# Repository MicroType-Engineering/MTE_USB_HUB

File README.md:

MTE_USB_HUB

As designed on the MicroType Engineering's YouTube series: https://youtu.be/uzqXgHHZUUs

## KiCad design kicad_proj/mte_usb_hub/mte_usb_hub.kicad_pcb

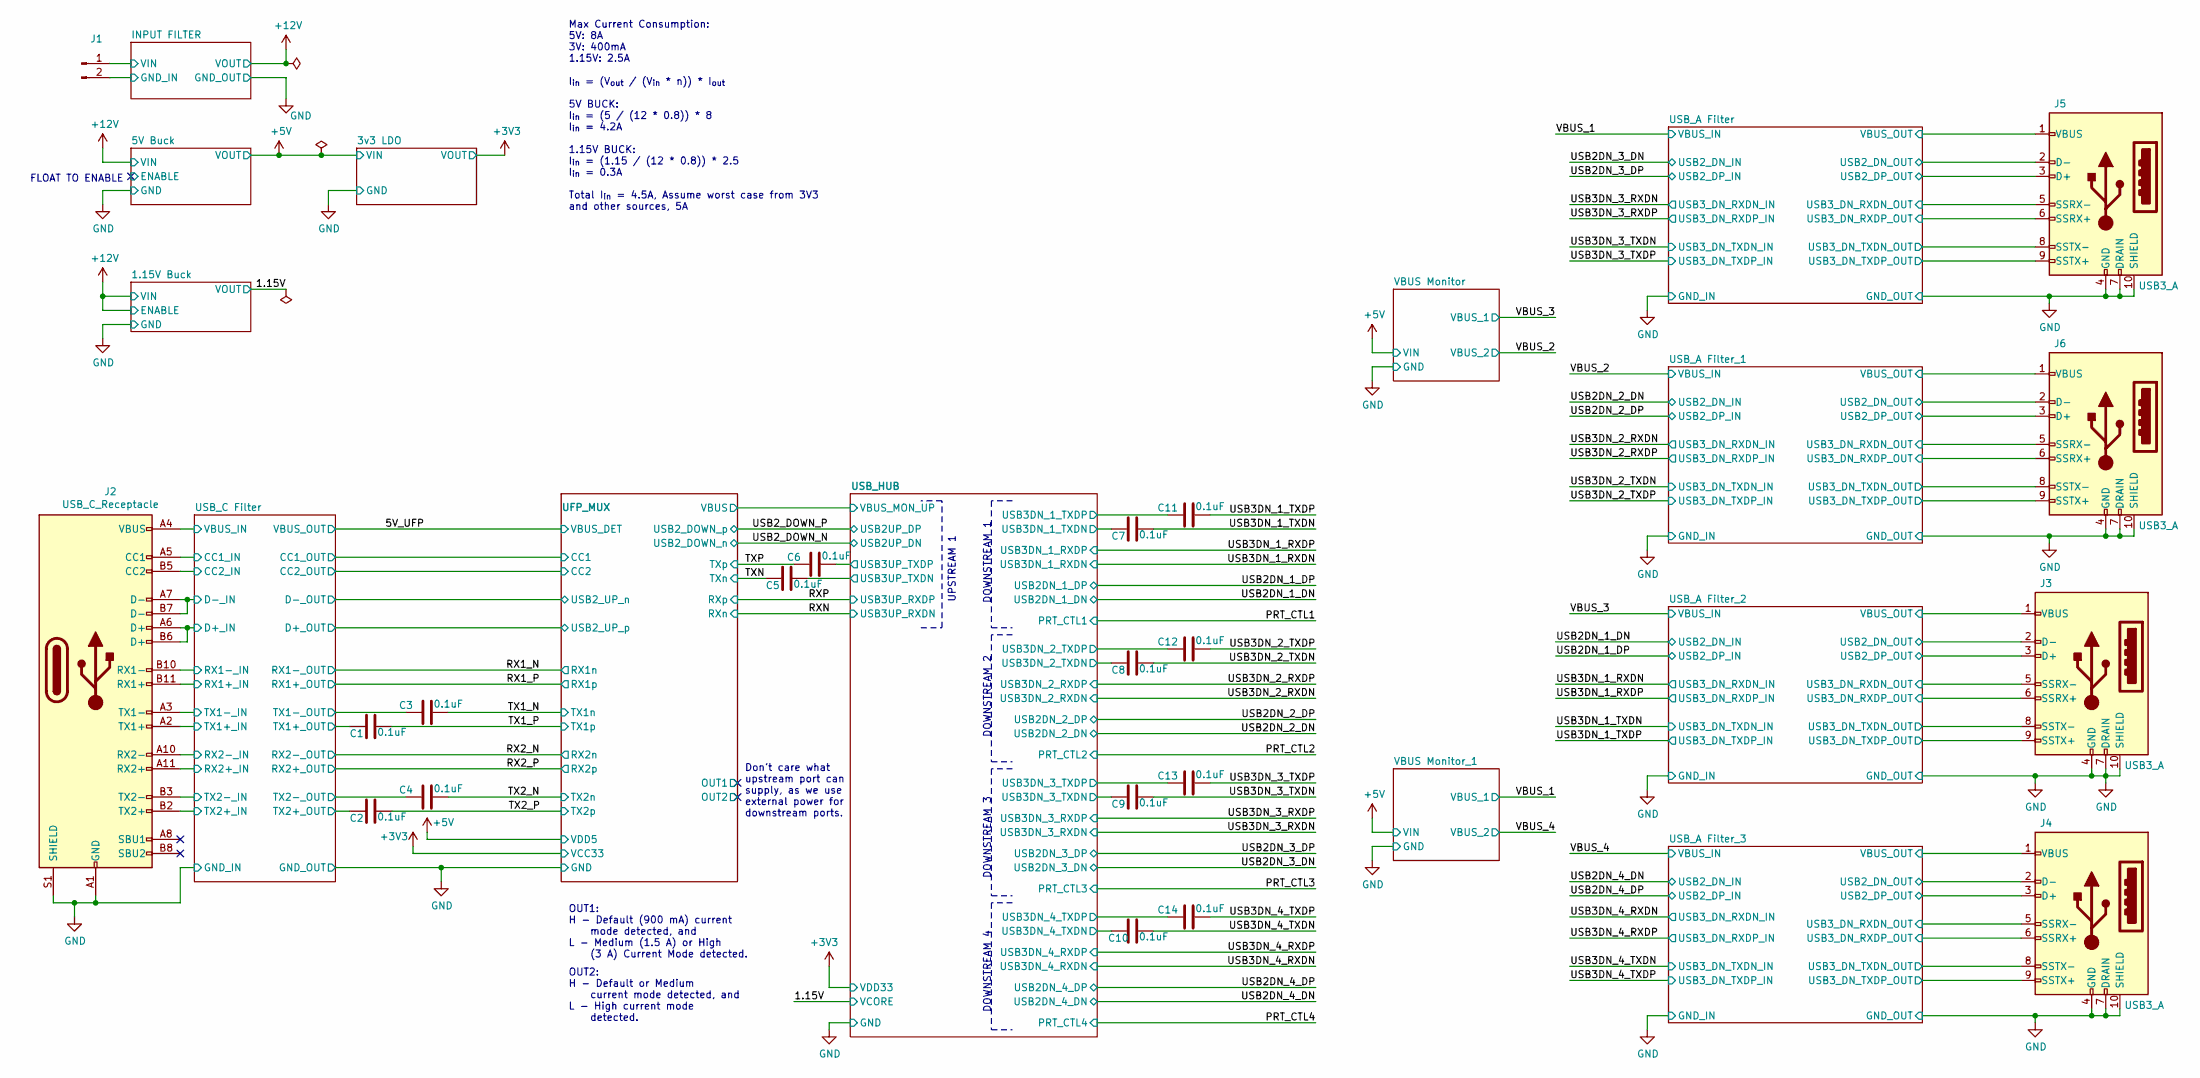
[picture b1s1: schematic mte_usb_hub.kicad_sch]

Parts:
C1, C2, C3, C4, C5, C6, C7, C8, C9, C10, C11, C12, C13, C14: CC0402KRX5R7BB104; CAPACITOR_0402N
J1: Conn_01x02_Male; PinHeader_1x02_P2.54mm_Vertical
J2: USB_C_Receptacle; USB_C_Receptacle_Amphenol_12401610E4-2A
J3, J4, J5, J6: USB3_A; USB3_A_Molex_48393-001

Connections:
/5V_UFP: J2.A4 (VBUS), J2.A9 (VBUS), J2.B4 (VBUS), J2.B9 (VBUS); also elsewhere on the board
/INPUT FILTER/GND_IN: J1.2; also elsewhere on the board
/INPUT FILTER/VIN: J1.1; also elsewhere on the board
/RX1_N: J2.B10 (RX1-); also elsewhere on the board
/RX1_P: J2.B11 (RX1+); also elsewhere on the board
/RX2_N: J2.A10 (RX2-); also elsewhere on the board
/RX2_P: J2.A11 (RX2+); also elsewhere on the board
/TX1_N: C3.2; also elsewhere on the board
/TX1_P: C1.2; also elsewhere on the board
/TX2_N: C4.2; also elsewhere on the board
/TX2_P: C2.2; also elsewhere on the board
/TXN: C5.1; also elsewhere on the board
/TXP: C6.1; also elsewhere on the board
/UFP_MUX/CC1: J2.A5 (CC1); also elsewhere on the board
/UFP_MUX/CC2: J2.B5 (CC2); also elsewhere on the board
/USB2DN_1_DN: J3.2 (D-); also elsewhere on the board
/USB2DN_1_DP: J3.3 (D+); also elsewhere on the board
/USB2DN_2_DN: J6.2 (D-); also elsewhere on the board
/USB2DN_2_DP: J6.3 (D+); also elsewhere on the board
/USB2DN_3_DN: J5.2 (D-); also elsewhere on the board
/USB2DN_3_DP: J5.3 (D+); also elsewhere on the board
/USB2DN_4_DN: J4.2 (D-); also elsewhere on the board
/USB2DN_4_DP: J4.3 (D+); also elsewhere on the board
/USB2_DOWN_N: J2.A7 (D-), J2.B7 (D-); also elsewhere on the board
/USB2_DOWN_P: J2.A6 (D+), J2.B6 (D+); also elsewhere on the board
/USB3DN_1_RXDN: J3.5 (SSRX-); also elsewhere on the board
/USB3DN_1_RXDP: J3.6 (SSRX+); also elsewhere on the board
/USB3DN_1_TXDN: C7.2, J3.8 (SSTX-); also elsewhere on the board
/USB3DN_1_TXDP: C11.2, J3.9 (SSTX+); also elsewhere on the board
/USB3DN_2_RXDN: J6.5 (SSRX-); also elsewhere on the board
/USB3DN_2_RXDP: J6.6 (SSRX+); also elsewhere on the board
/USB3DN_2_TXDN: C8.2, J6.8 (SSTX-); also elsewhere on the board
/USB3DN_2_TXDP: C12.2, J6.9 (SSTX+); also elsewhere on the board
/USB3DN_3_RXDN: J5.5 (SSRX-); also elsewhere on the board
/USB3DN_3_RXDP: J5.6 (SSRX+); also elsewhere on the board
/USB3DN_3_TXDN: C9.2, J5.8 (SSTX-); also elsewhere on the board
/USB3DN_3_TXDP: C13.2, J5.9 (SSTX+); also elsewhere on the board
/USB3DN_4_RXDN: J4.5 (SSRX-); also elsewhere on the board
/USB3DN_4_RXDP: J4.6 (SSRX+); also elsewhere on the board
/USB3DN_4_TXDN: C10.2, J4.8 (SSTX-); also elsewhere on the board
/USB3DN_4_TXDP: C14.2, J4.9 (SSTX+); also elsewhere on the board
/USB_C Filter/_TX1+: C1.1, J2.A2 (TX1+); also elsewhere on the board
/USB_C Filter/_TX1-: C3.1, J2.A3 (TX1-); also elsewhere on the board
/USB_C Filter/_TX2+: C2.1, J2.B2 (TX2+); also elsewhere on the board
/USB_C Filter/_TX2-: C4.1, J2.B3 (TX2-); also elsewhere on the board
/USB_HUB/USB3DN_1_TXDN: C7.1; also elsewhere on the board
/USB_HUB/USB3DN_1_TXDP: C11.1; also elsewhere on the board
/USB_HUB/USB3DN_2_TXDN: C8.1; also elsewhere on the board
/USB_HUB/USB3DN_2_TXDP: C12.1; also elsewhere on the board
/USB_HUB/USB3DN_3_TXDN: C9.1; also elsewhere on the board
/USB_HUB/USB3DN_3_TXDP: C13.1; also elsewhere on the board
/USB_HUB/USB3DN_4_TXDN: C10.1; also elsewhere on the board
/USB_HUB/USB3DN_4_TXDP: C14.1; also elsewhere on the board
/USB_HUB/USB3UP_TXDN: C5.2; also elsewhere on the board
/USB_HUB/USB3UP_TXDP: C6.2; also elsewhere on the board
/VBUS_1: J5.1 (VBUS); also elsewhere on the board
/VBUS_2: J6.1 (VBUS); also elsewhere on the board
/VBUS_3: J3.1 (VBUS); also elsewhere on the board
/VBUS_4: J4.1 (VBUS); also elsewhere on the board
GND: J2.A1 (GND), J2.A12 (GND), J2.B1 (GND), J2.B12 (GND), J2.S1 (SHIELD), J3.4 (GND), J3.7 (DRAIN), J3.10 (SHIELD), J4.4 (GND), J4.7 (DRAIN), J4.10 (SHIELD), J5.4 (GND), J5.7 (DRAIN), J5.10 (SHIELD), J6.4 (GND), J6.7 (DRAIN), J6.10 (SHIELD); also elsewhere on the board

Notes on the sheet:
FLOAT TO ENABLE
Max Current Consumption: 5V: 8A 3V: 400mA 1.15V: 2.5A
I_{in} = (V_{out} / (V_{in} * n)) * I_{out} 5V BUCK: I_{in} = (5 / (12 * 0.8)) * 8 I_{in} = 4.2A 1.15V BUCK: I_{in} = (1.15 / (12 * 0.8)) * 2.5 I_{in} = 0.3A Total I_{in} = 4.5A, Assume worst case from 3V3 and other sources, 5A
OUT1: H - Default (900 mA) current mode detected, and L - Medium (1.5 A) or High (3 A) Current Mode detected.
OUT2: H - Default or Medium current mode detected, and L - High current mode detected.
Don't care what upstream port can supply, as we use external power for downstream ports.
UPSTREAM 1
DOWNSTREAM 1
DOWNSTREAM 2
DOWNSTREAM 3
DOWNSTREAM 4

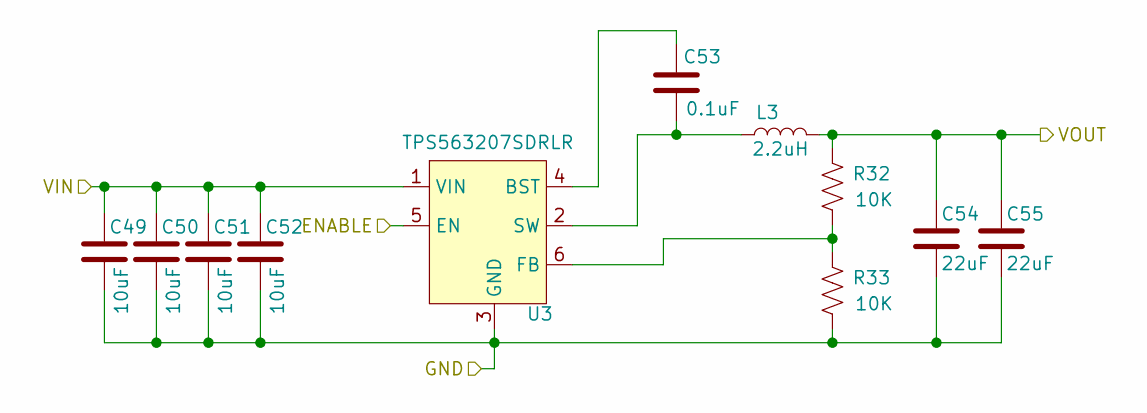
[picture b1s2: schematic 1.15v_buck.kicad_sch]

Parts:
C49, C50, C51, C52: GRM31CR71E106KA12L; CAPACITOR_1206N
C53: CC0402KRX5R7BB104; CAPACITOR_0402N
C54, C55: CL21A226MOCLRNC; CAPACITOR_0805N
L3: 74405042022; INDM400X400X200L95X310N
R32, R33: RC0402JR-0710KL; RESISTOR_0402N
U3: TPS563207SDRLR; SOL6P50_160X160X60L21N

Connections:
+12V: C49.1, C50.1, C51.1, C52.1, U3.1 (VIN), U3.5 (EN); also elsewhere on the board
/1.15V: C54.1, C55.1, L3.2, R32.1; also elsewhere on the board
GND: C49.2, C50.2, C51.2, C52.2, C54.2, C55.2, R33.2, U3.3 (GND); also elsewhere on the board
unnamed: C53.1, L3.1, U3.2 (SW)
unnamed: C53.2, U3.4 (BST)
unnamed: R32.2, R33.1, U3.6 (FB)

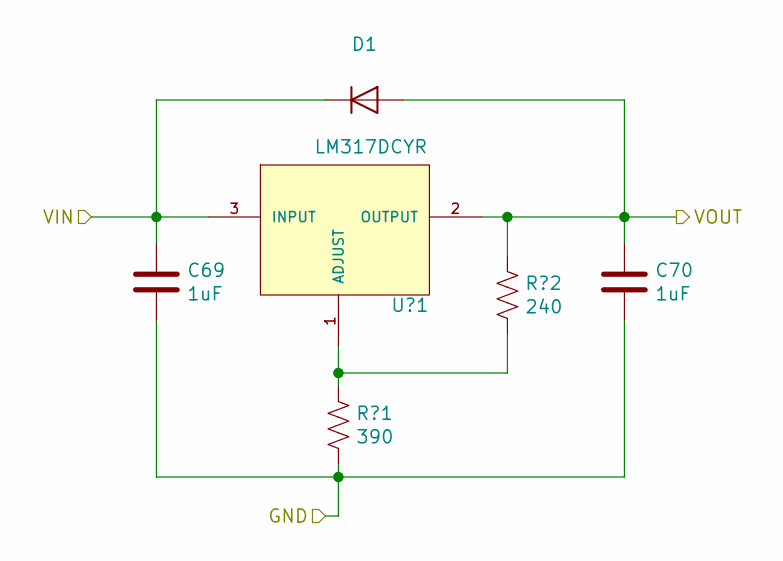
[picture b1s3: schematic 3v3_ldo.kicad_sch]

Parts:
C69, C70: CC0402KRX5R7BB105; CAPACITOR_0402N
D1: BAS16GWJ; SODFL360X160X130L45X62N
R?1: RC0402FR-07390RL; RESISTOR_0402N
R?2: RC0402JR-07240RL; RESISTOR_0402N
U?1: LM317DCYR; SOT223-4P230_700X180L80X75N

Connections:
+3V3: C70.1, D1.A, R?2.1, U?1.2 (OUTPUT), U?1.4 (OUTPUT); also elsewhere on the board
+5V: C69.1, D1.C (K), U?1.3 (INPUT); also elsewhere on the board
GND: C69.2, C70.2, R?1.2; also elsewhere on the board
unnamed: R?1.1, R?2.2, U?1.1 (ADJUST)

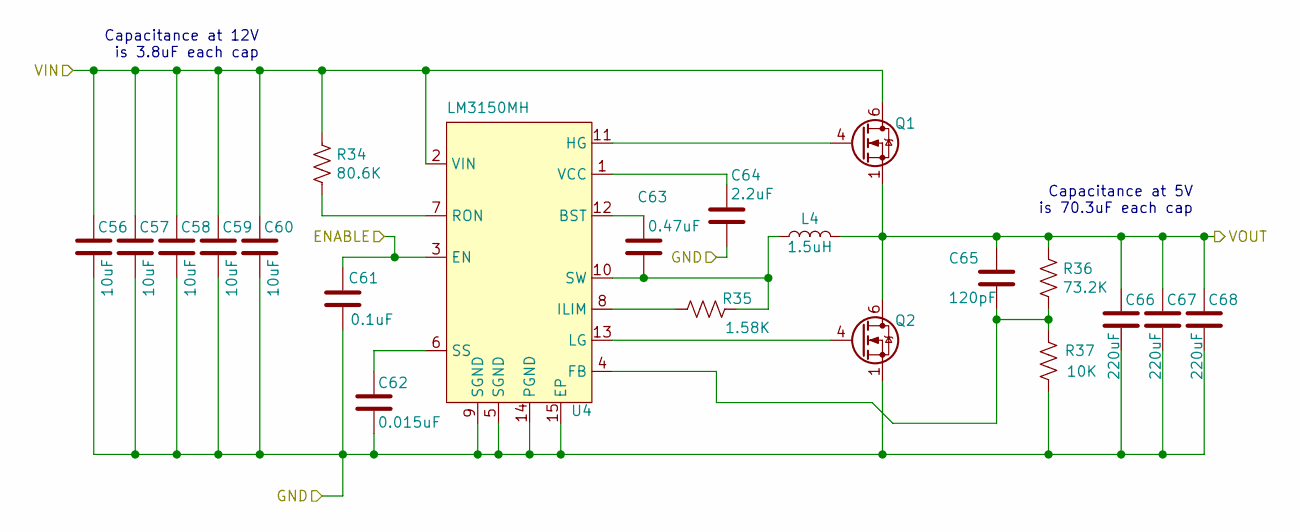
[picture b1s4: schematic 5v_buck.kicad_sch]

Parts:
C56, C57, C58, C59, C60: GRM31CR71E106KA12L; CAPACITOR_1206N
C61: CC0402KRX5R7BB104; CAPACITOR_0402N
C62: TMK105BJ153KV-F; CAPACITOR_0402N
C63: TMK105ABJ474KV-F; CAPACITOR_0402N
C64: TMK105CBJ225MV-F; CAPACITOR_0402N
C65: C0402C121J3GAC7867; CAPACITOR_0402N
C66, C67, C68: GRM32ER60J227ME05L; CAPACITOR_1210N
L4: SRP1270-1R5M; INDM1350X1350X700L250X300N
Q1: CSD16342Q5A
Q2: CSD17577Q5AT; CSD16342Q5A
R34: RC0402FR-0780K6L; RESISTOR_0402N
R35: RC0402FR-071K58L; RESISTOR_0402N
R36: RC0402FR-0773K2L; RESISTOR_0402N
R37: RC0402JR-0710KL; RESISTOR_0402N
U4: LM3150MH; SOP15P65_500X640X110L60X24T310X300N

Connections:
+5V: C65.1, C66.1, C67.1, C68.1, L4.2, Q1.1 (S), Q1.2 (S), Q1.3 (S), Q2.5 (D), Q2.6 (D), Q2.7 (D), Q2.8 (D), R36.1; also elsewhere on the board
+12V: C56.1, C57.1, C58.1, C59.1, C60.1, Q1.5 (D), Q1.6 (D), Q1.7 (D), Q1.8 (D), R34.1, U4.2 (VIN); also elsewhere on the board
/5V Buck/ENABLE: C61.2, U4.3 (EN)
GND: C56.2, C57.2, C58.2, C59.2, C60.2, C61.1, C62.2, C64.2, C66.2, C67.2, C68.2, Q2.1 (S), Q2.2 (S), Q2.3 (S), R37.2, U4.5 (SGND), U4.9 (SGND), U4.14 (PGND), U4.15 (EP); also elsewhere on the board
unnamed: C62.1, U4.6 (SS)
unnamed: C63.1, U4.12 (BST)
unnamed: C63.2, L4.1, R35.2, U4.10 (SW)
unnamed: C64.1, U4.1 (VCC)
unnamed: C65.2, R36.2, R37.1, U4.4 (FB)
unnamed: Q1.4 (G), U4.11 (HG)
unnamed: Q2.4 (G), U4.13 (LG)
unnamed: R34.2, U4.7 (RON)
unnamed: R35.1, U4.8 (ILIM)

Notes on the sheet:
Capacitance at 12V is 3.8uF each cap
Capacitance at 5V is 70.3uF each cap

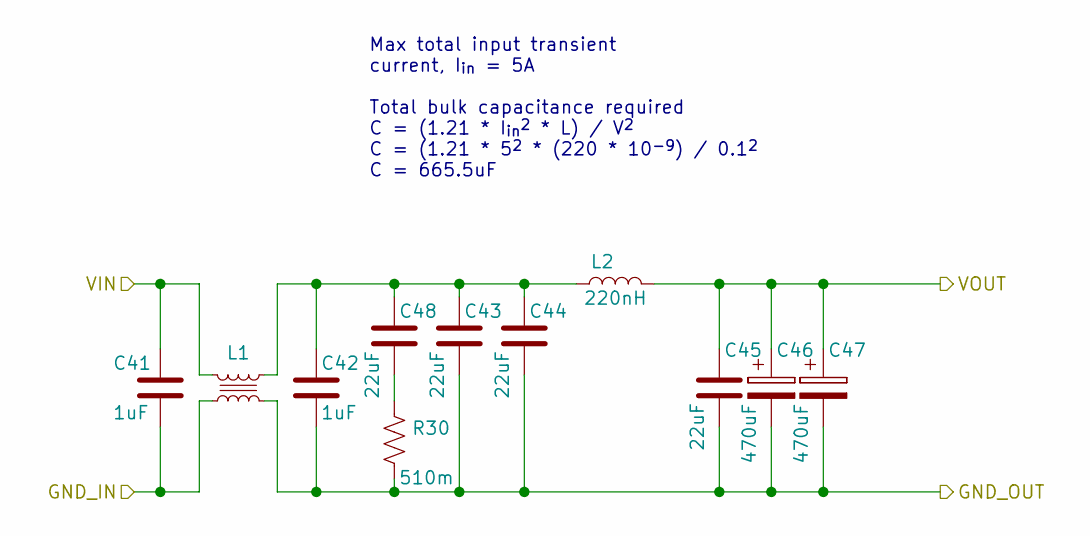
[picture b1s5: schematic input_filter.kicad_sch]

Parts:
C41, C42: CC0603KRX5R9BB105; CAPACITOR_0603N
C43, C44, C45, C48: GCJ32EC71E226KE02; CAPACITOR_1210N
C46, C47: EEE-HAE471UAP; CAPAE1030X1080L350X120N
L1: ACM1211-701-2PL-TL01
L2: FCUL0624-H-R22M=P3; INDM730X660X240L150X140N
R30: RL1206JR-070R51L; RESISTOR_1206N

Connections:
+12V: C45.1, C46.1, C47.1, L2.2; also elsewhere on the board
/INPUT FILTER/GND_IN: C41.2, L1.2; also elsewhere on the board
/INPUT FILTER/VIN: C41.1, L1.1; also elsewhere on the board
GND: C42.2, C43.2, C44.2, C45.2, C46.2, C47.2, L1.3, R30.2; also elsewhere on the board
unnamed: C42.1, C43.1, C44.1, C48.1, L1.4, L2.1
unnamed: C48.2, R30.1

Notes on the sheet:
Max total input transient current, I_{in} = 5A Total bulk capacitance required C = (1.21 * I_{in}^{2} * L) / V^{2} C = (1.21 * 5^{2} * (220 * 10^{-9}) / 0.1^{2} C = 665.5uF

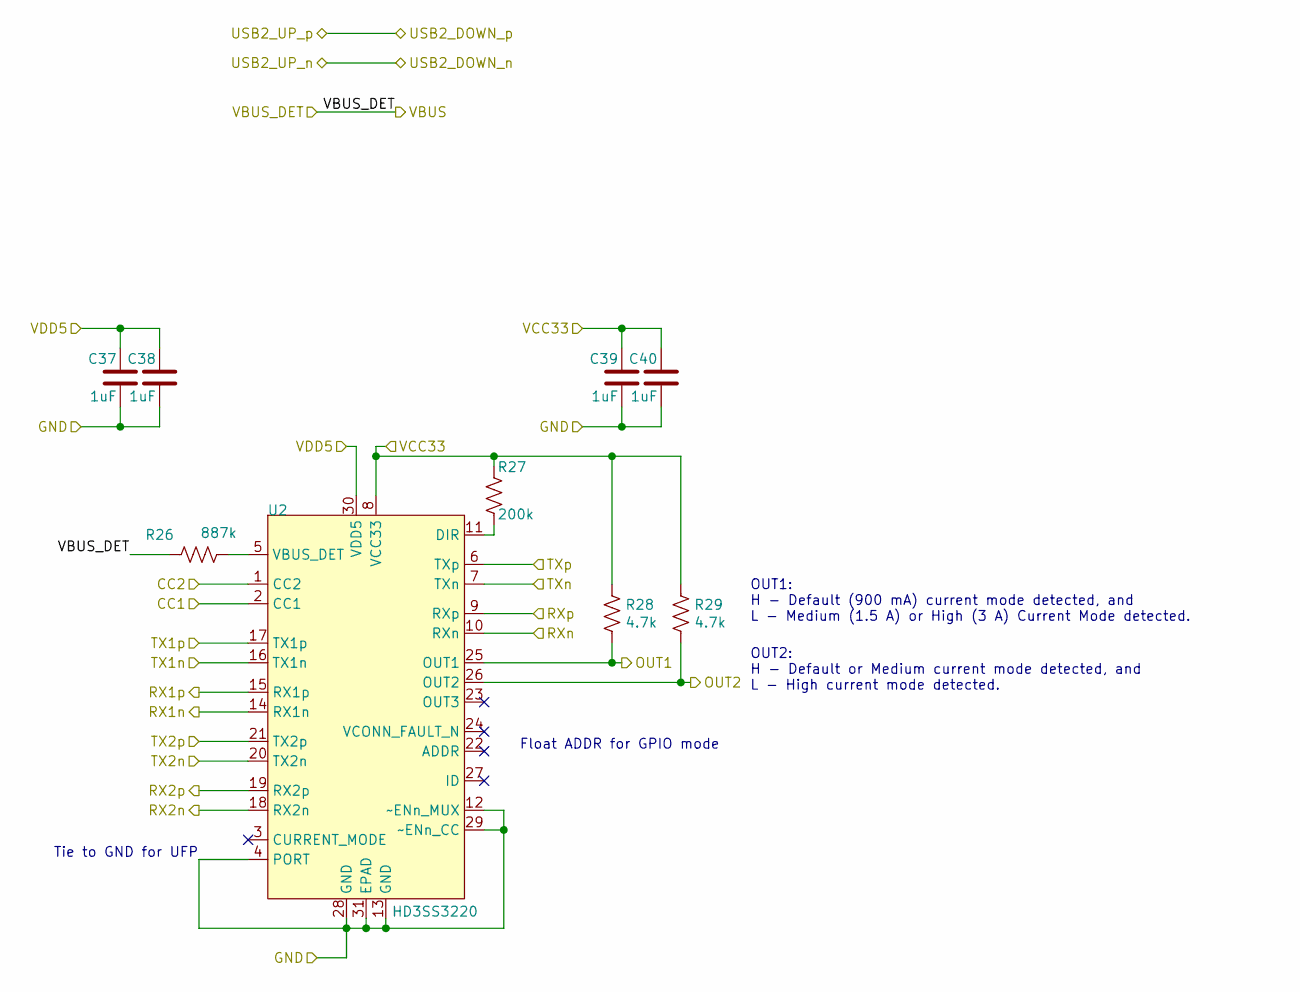
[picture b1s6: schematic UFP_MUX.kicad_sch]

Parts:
C37, C38, C39, C40: CC0402KRX5R7BB105; CAPACITOR_0402N
R26: RC0402FR-07887KL; RESISTOR_0402N
R27: RC0402JR-07200KL; RESISTOR_0402N
R28, R29: RC0402JR-074K7L; RESISTOR_0402N
U2: HD3SS3220; QFN31P40_250X450X80L30X20T120X320N

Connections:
+3V3: C39.1, C40.1, R27.1, R28.1, R29.1, U2.8 (VCC33); also elsewhere on the board
+5V: C37.1, C38.1, U2.30 (VDD5); also elsewhere on the board
/5V_UFP: R26.1; also elsewhere on the board
/RX1_N: U2.14 (RX1n); also elsewhere on the board
/RX1_P: U2.15 (RX1p); also elsewhere on the board
/RX2_N: U2.18 (RX2n); also elsewhere on the board
/RX2_P: U2.19 (RX2p); also elsewhere on the board
/RXN: U2.10 (RXn); also elsewhere on the board
/RXP: U2.9 (RXp); also elsewhere on the board
/TX1_N: U2.16 (TX1n); also elsewhere on the board
/TX1_P: U2.17 (TX1p); also elsewhere on the board
/TX2_N: U2.20 (TX2n); also elsewhere on the board
/TX2_P: U2.21 (TX2p); also elsewhere on the board
/TXN: U2.7 (TXn); also elsewhere on the board
/TXP: U2.6 (TXp); also elsewhere on the board
/UFP_MUX/CC1: U2.2 (CC1); also elsewhere on the board
/UFP_MUX/CC2: U2.1 (CC2); also elsewhere on the board
/UFP_MUX/OUT1: R28.2, U2.25 (OUT1)
/UFP_MUX/OUT2: R29.2, U2.26 (OUT2)
GND: C37.2, C38.2, C39.2, C40.2, U2.4 (PORT), U2.12 (~ENn_MUX), U2.13 (GND), U2.28 (GND), U2.29 (~ENn_CC), U2.31 (EPAD); also elsewhere on the board
unnamed: R26.2, U2.5 (VBUS_DET)
unnamed: R27.2, U2.11 (DIR)

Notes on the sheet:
Tie to GND for UFP
Float ADDR for GPIO mode
OUT1: H - Default (900 mA) current mode detected, and L - Medium (1.5 A) or High (3 A) Current Mode detected.
OUT2: H - Default or Medium current mode detected, and L - High current mode detected.

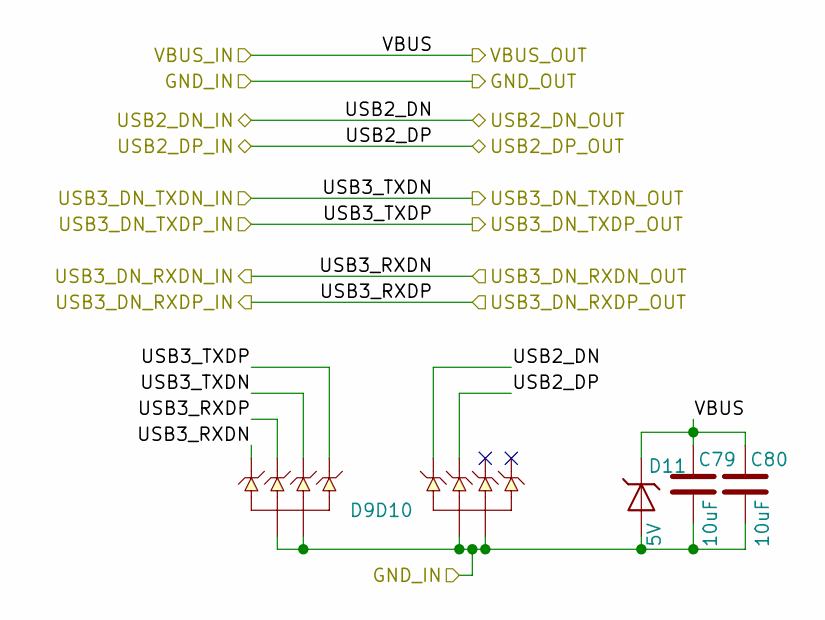
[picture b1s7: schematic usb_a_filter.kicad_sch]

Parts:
C79, C80: GRM21BR61H106ME43; CAPACITOR_0805N
D9, D10: ESD8004MUTAG
D11: ESD9X3.3ST5G; SODFL1006X43N

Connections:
/USB2DN_2_DN: D10.5, D10.6; also elsewhere on the board
/USB2DN_2_DP: D10.4, D10.7; also elsewhere on the board
/USB3DN_2_RXDN: D9.1, D9.10; also elsewhere on the board
/USB3DN_2_RXDP: D9.2, D9.9; also elsewhere on the board
/USB3DN_2_TXDN: D9.4, D9.7; also elsewhere on the board
/USB3DN_2_TXDP: D9.5, D9.6; also elsewhere on the board
/VBUS_2: C79.1, C80.1, D11.C; also elsewhere on the board
GND: C79.2, C80.2, D9.3, D9.8, D10.3, D10.8, D11.A; also elsewhere on the board

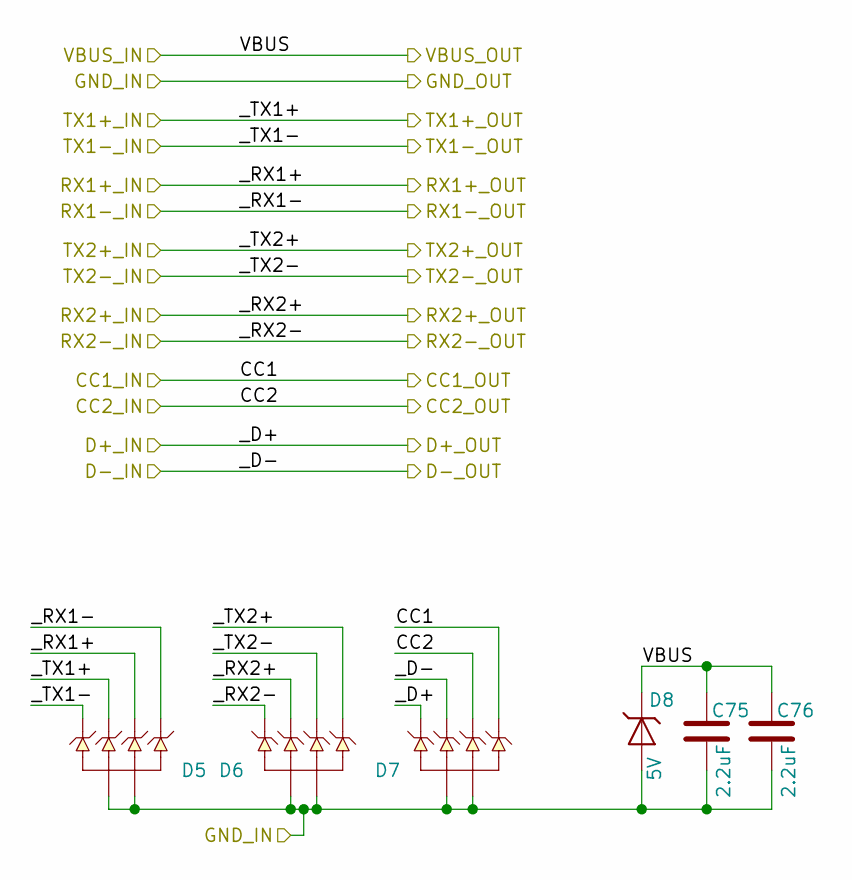
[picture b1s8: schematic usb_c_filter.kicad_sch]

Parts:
C75, C76: TMK105CBJ225MV-F; CAPACITOR_0402N
D5, D6, D7: ESD8004MUTAG
D8: ESD9X3.3ST5G; SODFL1006X43N

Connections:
/5V_UFP: C75.1, C76.1, D8.C; also elsewhere on the board
/RX1_N: D5.5, D5.6; also elsewhere on the board
/RX1_P: D5.4, D5.7; also elsewhere on the board
/RX2_N: D6.5, D6.6; also elsewhere on the board
/RX2_P: D6.4, D6.7; also elsewhere on the board
/UFP_MUX/CC1: D7.1, D7.10; also elsewhere on the board
/UFP_MUX/CC2: D7.2, D7.9; also elsewhere on the board
/USB2_DOWN_N: D7.4, D7.7; also elsewhere on the board
/USB2_DOWN_P: D7.5, D7.6; also elsewhere on the board
/USB_C Filter/_TX1+: D5.2, D5.9; also elsewhere on the board
/USB_C Filter/_TX1-: D5.1, D5.10; also elsewhere on the board
/USB_C Filter/_TX2+: D6.1, D6.10; also elsewhere on the board
/USB_C Filter/_TX2-: D6.2, D6.9; also elsewhere on the board
GND: C75.2, C76.2, D5.3, D5.8, D6.3, D6.8, D7.3, D7.8, D8.A; also elsewhere on the board

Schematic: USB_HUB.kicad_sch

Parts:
C15, C16, C17, C18, C19, C22, C25, C26, C27, C28, C29, C30, C31, C32, C33, C34, C35, C36: CC0402KRX5R7BB105; CAPACITOR_0402N
C20, C23: CC0402JRNPO9BN330; CAPACITOR_0402N
C21, C24: CC0402JRNPO9BN270; CAPACITOR_0402N
R1, R11, R20, R21, R22, R24, R25: RC0402JR-0710KL; RESISTOR_0402N
R2, R3, R4, R5, R6, R7, R8, R9, R10, R16, R17, R18, R19: RC0402JR-0747KL; RESISTOR_0402N
R12, R13, R14: RC0402JR-07200KL; RESISTOR_0402N
R15: RC0402JR-0710RL; RESISTOR_0402N
R23: RT0402DRE0712KL; RESISTOR_0402N
U1: USB7206; QFN101P40_1200X1200X90L60X20T800N
Y1: RH100-25.000-20-F-1030-TR; RH100-12.000-10-2020-EXT-TR

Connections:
+3V3: C28.1, C29.1, C30.1, C31.1, C32.1, C33.1, C34.1, C35.1, R1.2, R20.2, R21.2, R22.2, U1.26 (VDD33), U1.41 (~PRT_DIS_6_M), U1.42 (~PRT_DIS_6_P), U1.43 (VDD33), U1.53 (VDD33), U1.62 (VDD33), U1.67 (VDD33), U1.79 (VDD33), U1.81 (~PRT_DIS_5_P), U1.82 (~PRT_DIS_5_M), U1.88 (VDD33), U1.99 (VDD33); also elsewhere on the board
/1.15V: C15.1, C16.1, C17.1, C18.1, C19.1, C22.1, C25.1, C26.1, C27.1, U1.9 (VCORE), U1.18 (VCORE), U1.25 (VCORE), U1.31 (VCORE), U1.38 (VCORE), U1.55 (VCORE), U1.78 (VCORE), U1.85 (VCORE), U1.93 (VCORE); also elsewhere on the board
/5V_UFP: U1.2 (VBUS_MON_UP); also elsewhere on the board
/PRT_CTL1: U1.60 (PRT_CTL1/OCS)
/PRT_CTL2: U1.59 (PRT_CTL2/OCS)
/PRT_CTL3: U1.58 (PRT_CTL3/OCS)
/PRT_CTL4: U1.57 (PRT_CTL4/OCS)
/RXN: U1.95 (USB3UP_RXDM); also elsewhere on the board
/RXP: U1.94 (USB3UP_RXDP); also elsewhere on the board
/USB2DN_1_DN: U1.6 (USB2DN_1_DM); also elsewhere on the board
/USB2DN_1_DP: U1.5 (USB2DN_1_DP); also elsewhere on the board
/USB2DN_2_DN: U1.15 (USB2DN_2_DM); also elsewhere on the board
/USB2DN_2_DP: U1.14 (USB2DN_2_DP); also elsewhere on the board
/USB2DN_3_DN: U1.28 (USB2DN_3_DM); also elsewhere on the board
/USB2DN_3_DP: U1.27 (USB2DN_3_DP); also elsewhere on the board
/USB2DN_4_DN: U1.35 (USB2DN_4_DM); also elsewhere on the board
/USB2DN_4_DP: U1.34 (USB2DN_4_DP); also elsewhere on the board
/USB2_DOWN_N: U1.90 (USB2UP_DM); also elsewhere on the board
/USB2_DOWN_P: U1.89 (USB2UP_DP); also elsewhere on the board
/USB3DN_1_RXDN: U1.11 (USB3DN_1_RXDM); also elsewhere on the board
/USB3DN_1_RXDP: U1.10 (USB3DN_1_RXDP); also elsewhere on the board
/USB3DN_2_RXDN: U1.17 (USB3DN_2_TXDM); also elsewhere on the board
/USB3DN_2_RXDP: U1.16 (USB3DN_2_TXDP); also elsewhere on the board
/USB3DN_3_RXDN: U1.30 (USB3DN_3_TXDM); also elsewhere on the board
/USB3DN_3_RXDP: U1.29 (USB3DN_3_TXDP); also elsewhere on the board
/USB3DN_4_RXDN: U1.37 (USB3DN_4_TXDM); also elsewhere on the board
/USB3DN_4_RXDP: U1.36 (USB3DN_4_TXDP); also elsewhere on the board
/USB_HUB/USB3DN_1_TXDN: U1.8 (USB3DN_1_TXDM); also elsewhere on the board
/USB_HUB/USB3DN_1_TXDP: U1.7 (USB3DN_1_TXDP); also elsewhere on the board
/USB_HUB/USB3DN_2_TXDN: U1.20 (USB3DN_2_RXDM); also elsewhere on the board
/USB_HUB/USB3DN_2_TXDP: U1.19 (USB3DN_2_RXDP); also elsewhere on the board
/USB_HUB/USB3DN_3_TXDN: U1.33 (USB3DN_3_RXDM); also elsewhere on the board
/USB_HUB/USB3DN_3_TXDP: U1.32 (USB3DN_3_RXDP); also elsewhere on the board
/USB_HUB/USB3DN_4_TXDN: U1.40 (USB3DN_4_RXDM); also elsewhere on the board
/USB_HUB/USB3DN_4_TXDP: U1.39 (USB3DN_4_RXDP); also elsewhere on the board
/USB_HUB/USB3UP_TXDN: U1.92 (USB3UP_TXDM); also elsewhere on the board
/USB_HUB/USB3UP_TXDP: U1.91 (USB3UP_TXDP); also elsewhere on the board
GND: C15.2, C16.2, C17.2, C18.2, C19.2, C20.2, C22.2, C23.2, C25.2, C26.2, C27.2, C28.2, C29.2, C30.2, C31.2, C32.2, C33.2, C34.2, C35.2, C36.2, R2.1, R3.1, R4.1, R5.1, R6.1, R7.1, R8.1, R9.1, R10.1, R11.2, R12.2, R13.2, R14.2, R15.1, R16.1, R17.1, R18.1, R19.1, R23.2, R24.2, R25.2, U1.24 (TESTEN), U1.101 (VSS), Y1.1, Y1.3; also elsewhere on the board
unnamed: C20.1, U1.97 (XTALO), Y1.4
unnamed: C36.1, R1.1, U1.1 (RESET_N)
unnamed: R2.2, U1.44 (I2S_SDI)
unnamed: R3.2, U1.45 (I2S_SDO)
unnamed: R4.2, U1.46 (I2S_CLK)
unnamed: R5.2, U1.47 (I2S_LRCK)
unnamed: R6.2, U1.48 (I2S_MCLK)
unnamed: R7.2, U1.61 (MSTR_I2C_CLK)
unnamed: R8.2, U1.3 (MSTR_I2C_DATA)
unnamed: R9.2, U1.75 (SLV_I2C_CLK)
unnamed: R10.2, U1.76 (SLV_I2C_DAT)
unnamed: R11.1, U1.21 (~CFG_STRAP_1)
unnamed: R12.1, U1.22 (~CFG_STRAP_2)
unnamed: R13.1, U1.23 (~CFG_STRAP_3)
unnamed: R14.1, U1.69 (~CFG_NON_REM)
unnamed: R15.2, U1.70 (~CFG_BC_EN)
unnamed: R16.2, U1.68 (SPI_CLK)
unnamed: R17.2, U1.71 (SPI_D1)
unnamed: R18.2, U1.72 (SPI_D2)
unnamed: R19.2, U1.73 (SPI_D3)
unnamed: R20.1, U1.63 (TEST_1)
unnamed: R21.1, U1.64 (TEST_2)
unnamed: R22.1, U1.65 (TEST_3)
unnamed: R23.1, U1.100 (RBIAS)
unnamed: R24.1, U1.86 (USB3DN_5_RXDP)
unnamed: R25.1, U1.87 (USB3DN_5_RXDM)
unnamed: C23.1, U1.98 (XTALI/CLK_IN), Y1.2

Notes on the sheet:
27pF assume Cstray = 6.5pF 33pF assume Cstray = 3.5pF
CL = (c^{2} / 2c) + C_{stray}
DCP and CDP battery charging on ports 1-4
I2S disabled
I2C disabled
SPI disabled
Only valid config for ~{CFG_STRAP_X and test pins as per datasheet}
All ports removable
Place near IC, connect to GND plane
By default, all ports are configured to non-split mode. PRT_CTLX_U3 floar when not using PortSplit
Unused USB2DN tie to 3v3
Unused USB3DN_TX Float
Unused USB3DN_RX Weak pulldown

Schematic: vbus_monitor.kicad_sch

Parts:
C77, C78: GRM21BR61H106ME43; CAPACITOR_0805N
U6: UCS2114

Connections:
+5V: C77.1, C78.1, U6.3 (COMM_ILIM), U6.6 (V_S), U6.7 (V_S), U6.8 (VDD), U6.9 (VS), U6.10 (VS); also elsewhere on the board
/VBUS_1: U6.4 (VBUS_1), U6.5 (VBUS_1); also elsewhere on the board
/VBUS_4: U6.11 (VBUS_2), U6.12 (VBUS_2); also elsewhere on the board
GND: C77.2, C78.2, U6.1 (PWR_EN_1), U6.2 (GND), U6.13 (BOOST#), U6.14 (GND), U6.15 (PWR_EN_2), U6.16 (~ALERT_2), U6.17 (GND), U6.18 (SMDATA), U6.19 (SMCLK), U6.20 (~ALERT_1); also elsewhere on the board

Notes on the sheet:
EN Active-Low
ILIM = 3.2A

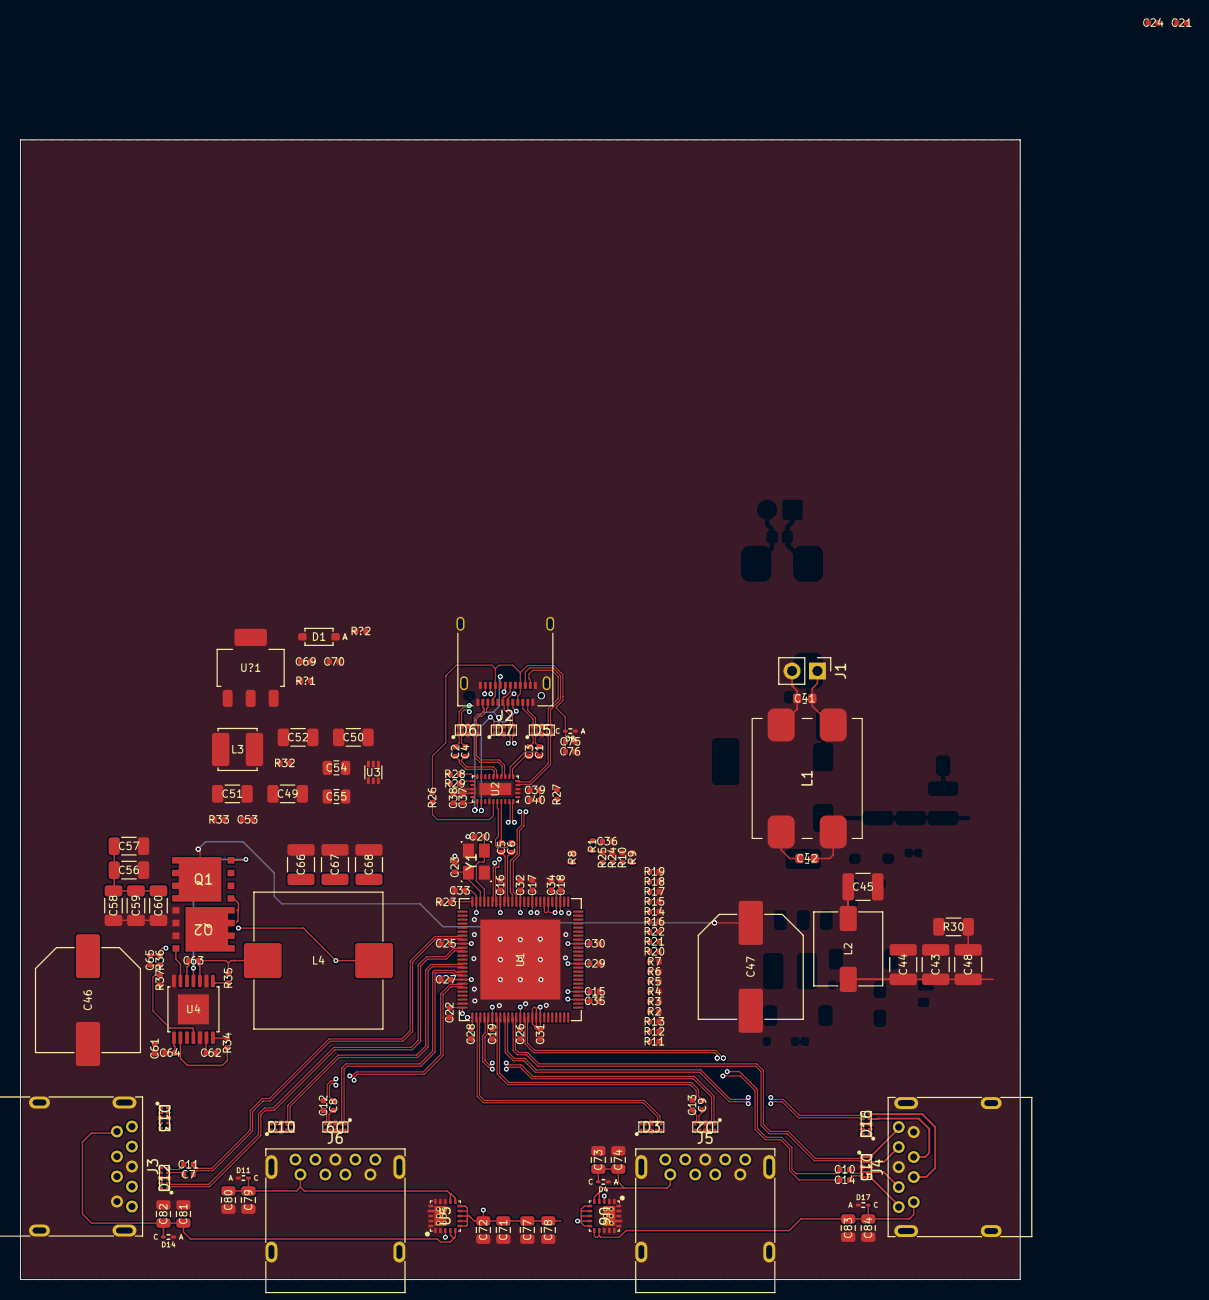
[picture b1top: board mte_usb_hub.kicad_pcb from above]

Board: 6 copper layers, 100.0 x 114.0 mm, 159 parts (0 on the bottom side), 113 nets.

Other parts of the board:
C71, C72, C73, C74, C81, C82, C83, C84: GRM21BR61H106ME43; CAPACITOR_0805N
D2, D3, D12, D13, D15, D16: ESD8004MUTAG
D4, D14, D17: ESD9X3.3ST5G; SODFL1006X43N
U5: UCS2114

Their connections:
+5V: C71.1, C72.1, U5.3 (COMM_ILIM), U5.6 (V_S), U5.7 (V_S), U5.8 (VDD), U5.9 (VS), U5.10 (VS); also elsewhere on the board
/USB2DN_1_DN: D13.5, D13.6; also elsewhere on the board
/USB2DN_1_DP: D13.4, D13.7; also elsewhere on the board
/USB2DN_3_DN: D3.5, D3.6; also elsewhere on the board
/USB2DN_3_DP: D3.4, D3.7; also elsewhere on the board
/USB2DN_4_DN: D16.5, D16.6; also elsewhere on the board
/USB2DN_4_DP: D16.4, D16.7; also elsewhere on the board
/USB3DN_1_RXDN: D12.1, D12.10; also elsewhere on the board
/USB3DN_1_RXDP: D12.2, D12.9; also elsewhere on the board
/USB3DN_1_TXDN: D12.4, D12.7; also elsewhere on the board
/USB3DN_1_TXDP: D12.5, D12.6; also elsewhere on the board
/USB3DN_3_RXDN: D2.1, D2.10; also elsewhere on the board
/USB3DN_3_RXDP: D2.2, D2.9; also elsewhere on the board
/USB3DN_3_TXDN: D2.4, D2.7; also elsewhere on the board
/USB3DN_3_TXDP: D2.5, D2.6; also elsewhere on the board
/USB3DN_4_RXDN: D15.1, D15.10; also elsewhere on the board
/USB3DN_4_RXDP: D15.2, D15.9; also elsewhere on the board
/USB3DN_4_TXDN: D15.4, D15.7; also elsewhere on the board
/USB3DN_4_TXDP: D15.5, D15.6; also elsewhere on the board
/VBUS_1: C73.1, C74.1, D4.C; also elsewhere on the board
/VBUS_2: U5.11 (VBUS_2), U5.12 (VBUS_2); also elsewhere on the board
/VBUS_3: C81.1, C82.1, D14.C, U5.4 (VBUS_1), U5.5 (VBUS_1); also elsewhere on the board
/VBUS_4: C83.1, C84.1, D17.C; also elsewhere on the board
GND: C71.2, C72.2, C73.2, C74.2, C81.2, C82.2, C83.2, C84.2, D2.3, D2.8, D3.3, D3.8, D4.A, D12.3, D12.8, D13.3, D13.8, D14.A, D15.3, D15.8, D16.3, D16.8, D17.A, U5.1 (PWR_EN_1), U5.2 (GND), U5.13 (BOOST#), U5.14 (GND), U5.15 (PWR_EN_2), U5.16 (~ALERT_2), U5.17 (GND), U5.18 (SMDATA), U5.19 (SMCLK), U5.20 (~ALERT_1); also elsewhere on the board

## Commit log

2021-03-16 Parts created from video one
2021-03-17 Initial setup of USB hub configurations
2021-03-17 Changes sheet pwr location
    Mainly to test Discord Webhook
2021-03-19 Finishes upstream USB setup
    No power setup, no downstream ports setup
2021-03-19 Starts downstream ports
2021-03-19 Final tweaks for the video
2021-04-11 Fixes Tx1/Tx2 being swapped from USB C UFP
2021-04-11 Starts power design
    Input buck started from 12V -> 5V. One per 2 ports
2021-04-13 Continues power design, replaces Micron Buck with a TI
    Micron had a trash datasheet
2021-04-15 New buck regulator added
2021-04-15 Adds 1v15 buck
2021-04-24 Adds 3v3 LDO
2021-04-24 Implements VBUS monitor, starts ESD protection
2021-04-28 Finishes input filter, minor buck changes
2021-04-28 Adds bulk capacitors on 12V input
2021-05-31 Updates input protection, output BC enabled
2021-06-12 New changes from the livestream
    Starts the layout
2021-06-26 Fixes the broken FET footprint, updates to latest nightly
2021-06-26 Updates from the livestream
2021-07-17 Livestream updates
